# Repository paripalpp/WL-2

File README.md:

# WL-2
This boad make M5 stamp pico connections to im920s and USB and CAN(TWAI), onboad downloader. 
All connections are noted on the boad with silk.
 
 Testing now

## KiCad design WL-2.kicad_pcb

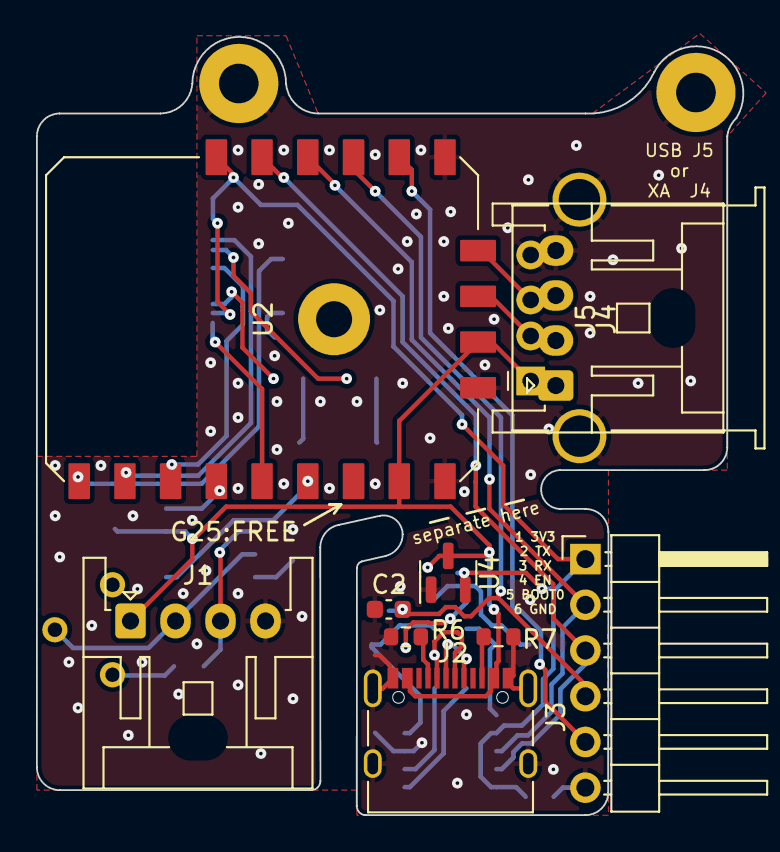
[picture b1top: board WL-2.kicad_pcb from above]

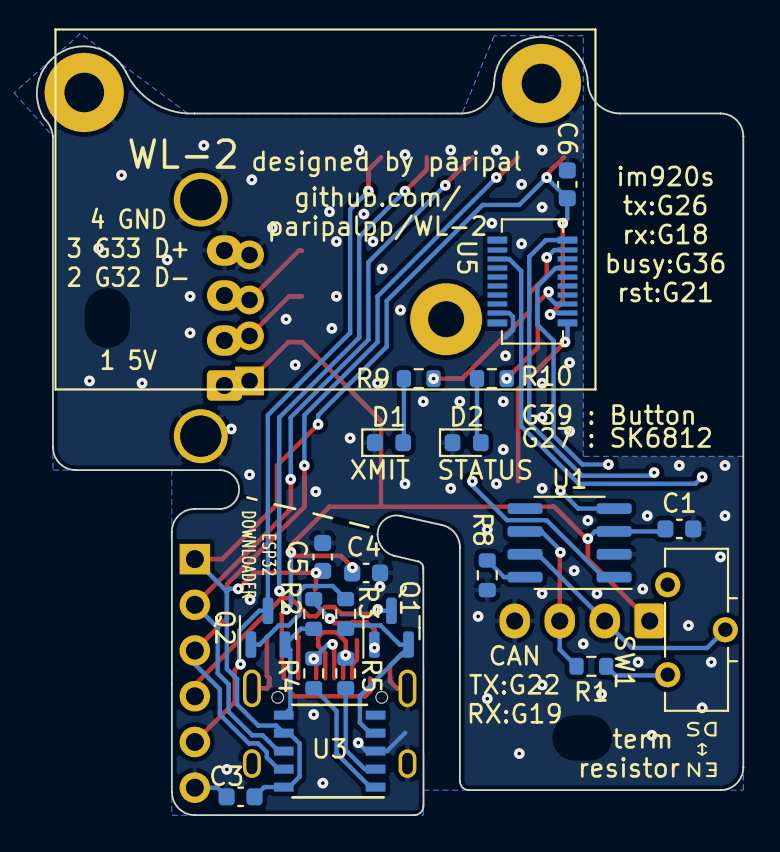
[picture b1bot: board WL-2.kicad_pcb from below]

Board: 2 copper layers, 39.2 x 43.2 mm, 31 parts (21 on the bottom side), 33 nets.

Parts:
C1, C2, C3, C6: 100n; C_0603_1608Metric
C4, C5: 1u; C_0603_1608Metric
D1, D2: LED; LED_0603_1608Metric
J1, J4: Conn_01x04_Female; JST_XA_S04B-XASK-1_1x04_P2.50mm_Horizontal
J2: USB_C_Receptacle_USB2.0; USB_C_Receptacle_XKB_U262-16XN-4BVC11
J3: Conn_01x06_Male; PinHeader_1x06_P2.54mm_Horizontal
J5: USB_A; USB_A_Stewart_SS-52100-001_Horizontal
Q1, Q2: Q_NPN_BEC; SOT-23
R1: 120; R_0603_1608Metric
R2, R3, R8, R9, R10: 10k; R_0603_1608Metric
R4, R5: 22; R_0603_1608Metric
R6, R7: 5.1k; R_0603_1608Metric
SW1: SW_SPDT; IS-1245T-G
U1: MCP2551-I-SN; SOIC-8_3.9x4.9mm_P1.27mm
U2: M5STAMP-PICO
U3: CH340K; SSOP-10_3.9x4.9mm_P1.00mm
U4: MCP1703A-3302_SOT23; SOT-23
U5: IM920s

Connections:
+3V3: C3.1, C5.1, C6.1, J3.1, U2.19 (3V3), U3.7 (VCC), U3.10 (V3), U4.2 (VO), U5.17 (VCC)
+5V: C1.1, C4.1, J1.1, J2.A4 (VBUS), J2.A9 (VBUS), J2.B4 (VBUS), J2.B9 (VBUS), J4.1, J5.1 (VBUS), U1.3 (VDD), U2.8 (5V), U2.11 (5V), U4.3 (VI)
/CANH: J1.2, SW1.2 (B), U1.7 (CANH)
/CANL: J1.3, R1.2, U1.6 (CANL)
/boot0: J3.5, Q2.3 (C), U2.15 (G0/BOOT0)
/canrx: U1.4 (RXD), U2.4 (G19)
/cantx: U1.1 (TXD), U2.6 (G22)
/dm: J2.A7 (D-), J2.B7 (D-), R5.1
/dp: J2.A6 (D+), J2.B6 (D+), R4.2
/en: C2.1, J3.4, Q1.3 (C), U2.16 (EN)
/im920busy: U2.2 (G36), U5.1 (IO1/BUSY)
/im920rst: U2.5 (G21), U5.19 (RESET)
/im920rx: U2.3 (G18), U5.7 (IO7/TxD)
/im920status: R10.2, U5.15 (STATUS)
/im920tx: U2.1 (G26), U5.6 (IO6/RxD)
/im920xmit: R9.2, U5.3 (IO3/XMIT)
/uartrx: J4.3, J5.3 (D+), U2.13 (G33)
/uarttx: J4.2, J5.2 (D-), U2.12 (G32)
/vcprx: J3.3, U2.18 (G1/Tx0), U3.9 (RXD)
/vcptx: J3.2, U2.17 (G3/Rx0), U3.8 (TXD)
/~dtr: Q1.2 (E), R3.2, U3.4 (~DTR)
/~rts: Q2.2 (E), R2.2, U3.6 (~RTS)
GND: C1.2, C2.2, C3.2, C4.2, C5.2, C6.2, D1.1 (K), D2.1 (K), J1.4, J2.A1 (GND), J2.A12 (GND), J2.B1 (GND), J2.B12 (GND), J2.S1 (SHIELD), J3.6, J4.4, J5.4 (GND), J5.5 (Shield), R6.1, R7.1, R8.1, U1.2 (VSS), U2.9 (GND), U2.10 (GND), U2.14 (GND), U3.3 (GND), U4.1 (GND), U5.18 (GND)
unnamed: D1.2 (A), R9.1
unnamed: D2.2 (A), R10.1
unnamed: J2.A5 (CC1), R6.2
unnamed: J2.B5 (CC2), R7.2
unnamed: Q1.1 (B), R2.1
unnamed: Q2.1 (B), R3.1
unnamed: R1.1, SW1.1 (A)
unnamed: R4.1, U3.1 (UD+)
unnamed: R5.2, U3.2 (UD-)
unnamed: R8.2, U1.8 (Rs)

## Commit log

2022-05-15 pcb writing finished
2022-05-16 im920 added
2022-05-16 completed
2022-05-16 Create LICENSE
